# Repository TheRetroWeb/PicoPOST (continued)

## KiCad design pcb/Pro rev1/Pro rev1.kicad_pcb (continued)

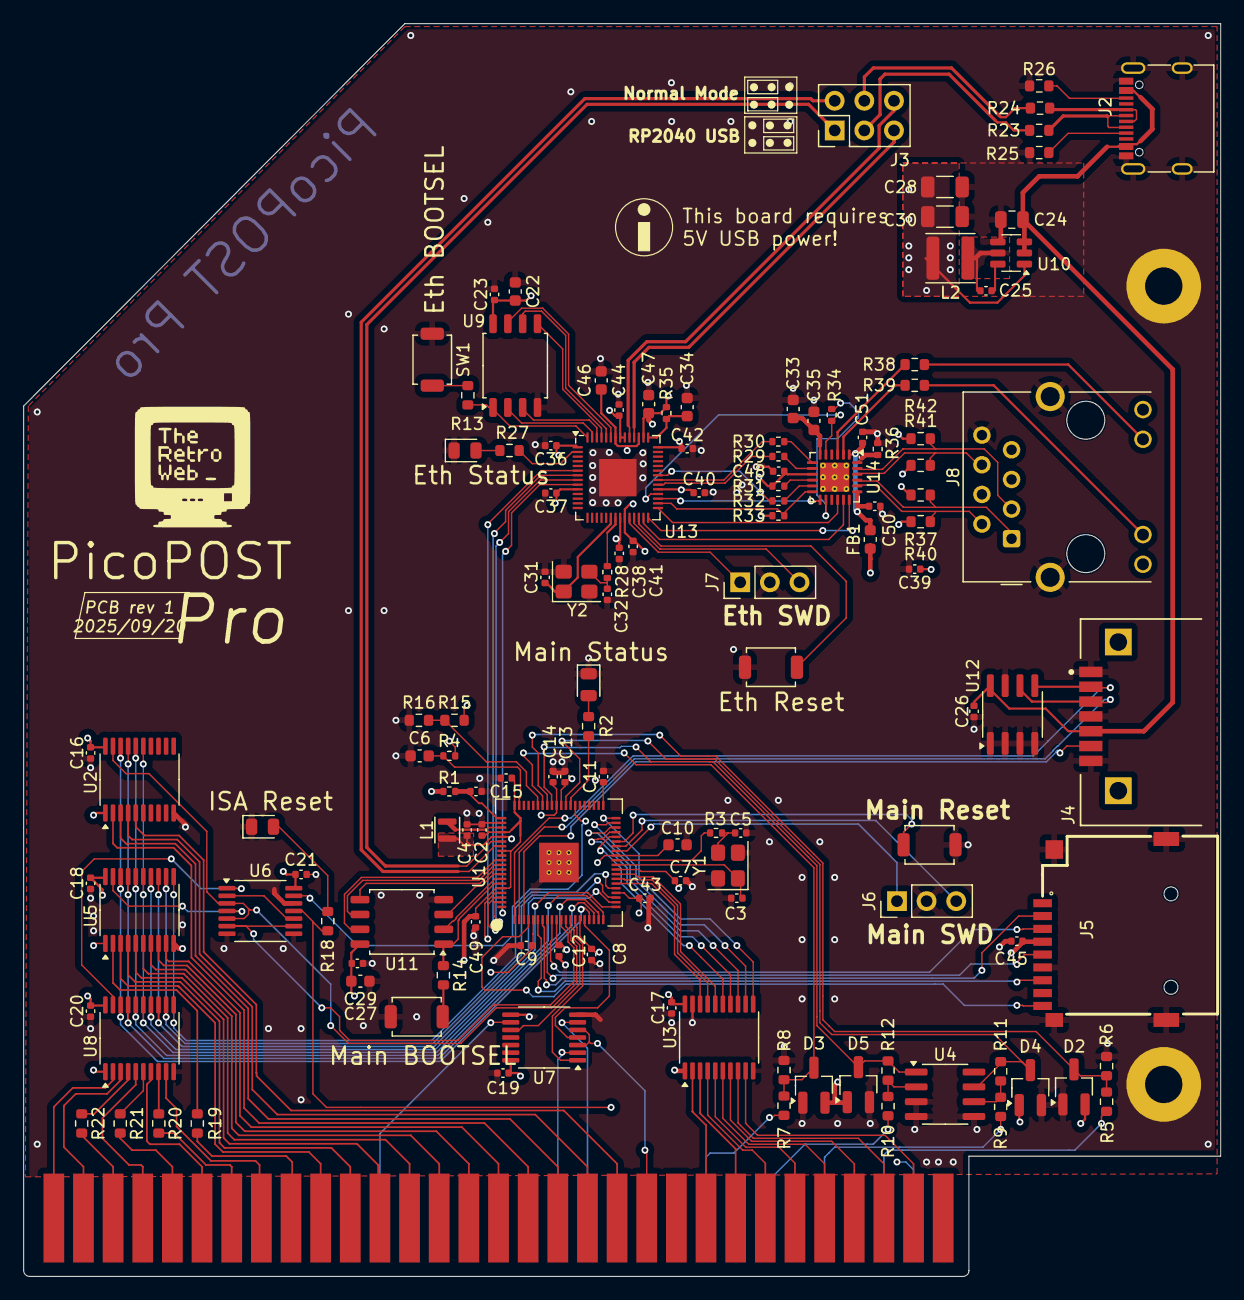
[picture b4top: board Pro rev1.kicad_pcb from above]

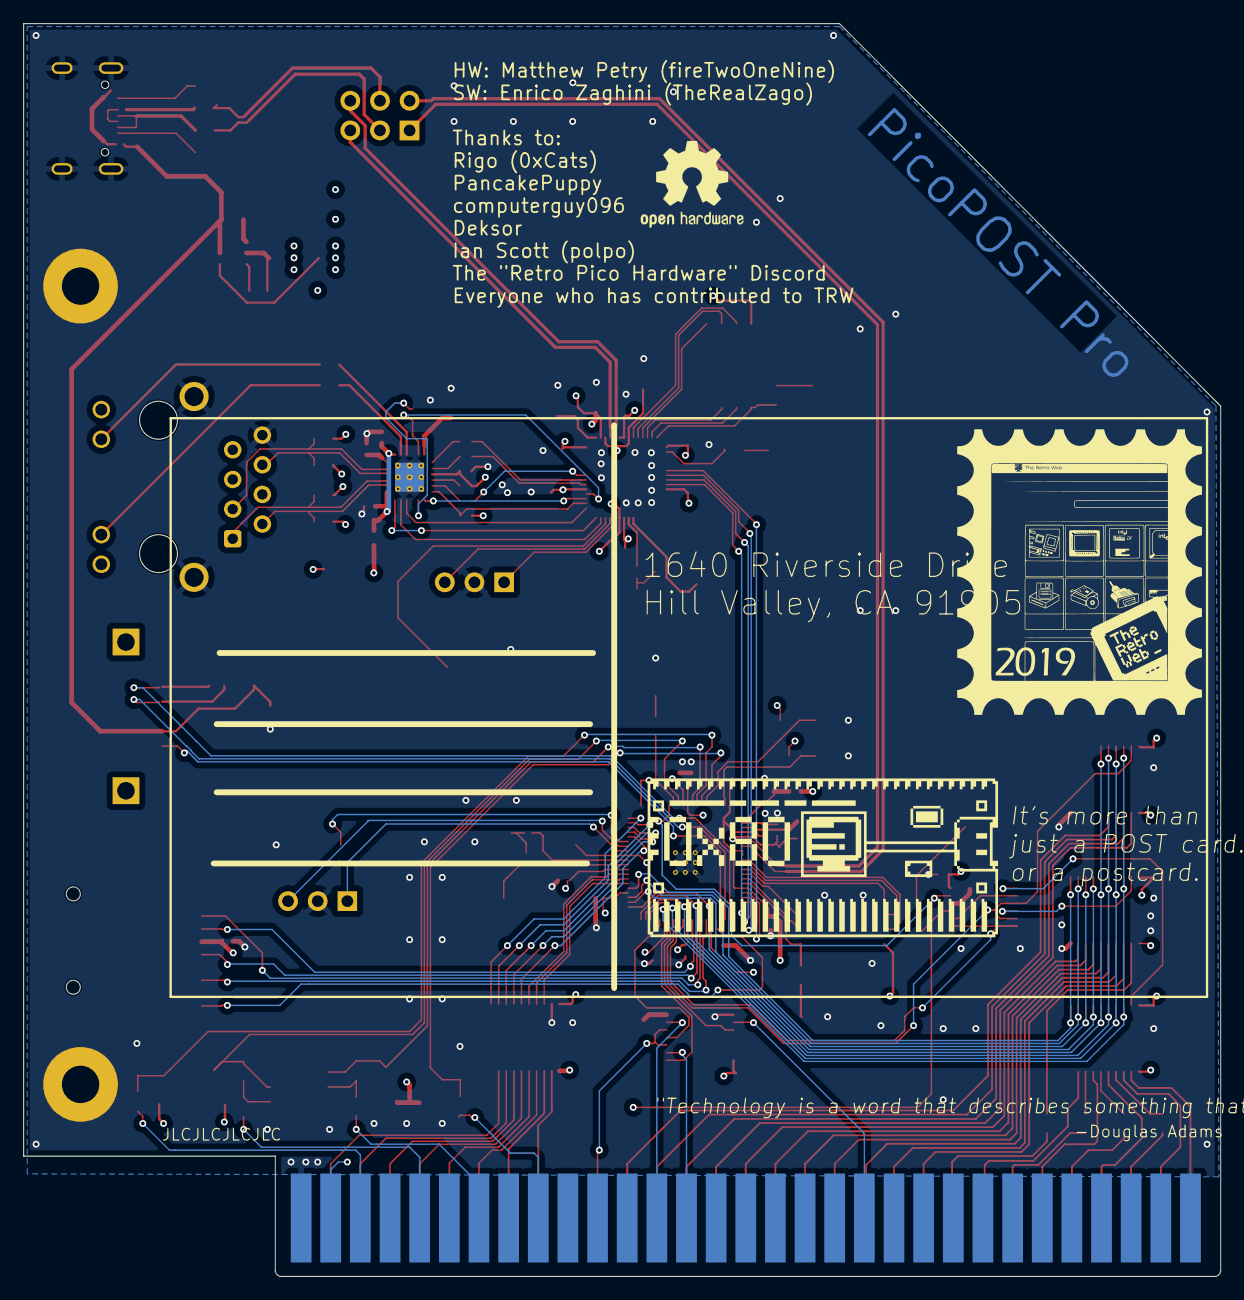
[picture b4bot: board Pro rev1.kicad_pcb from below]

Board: 4 copper layers, 102.6 x 107.3 mm, 135 parts (2 on the bottom side), 162 nets.

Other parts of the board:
.: LOGO; TRW_logo
.#2: LOGO; postcard_stamp
.#3: LOGO; picopost_logo

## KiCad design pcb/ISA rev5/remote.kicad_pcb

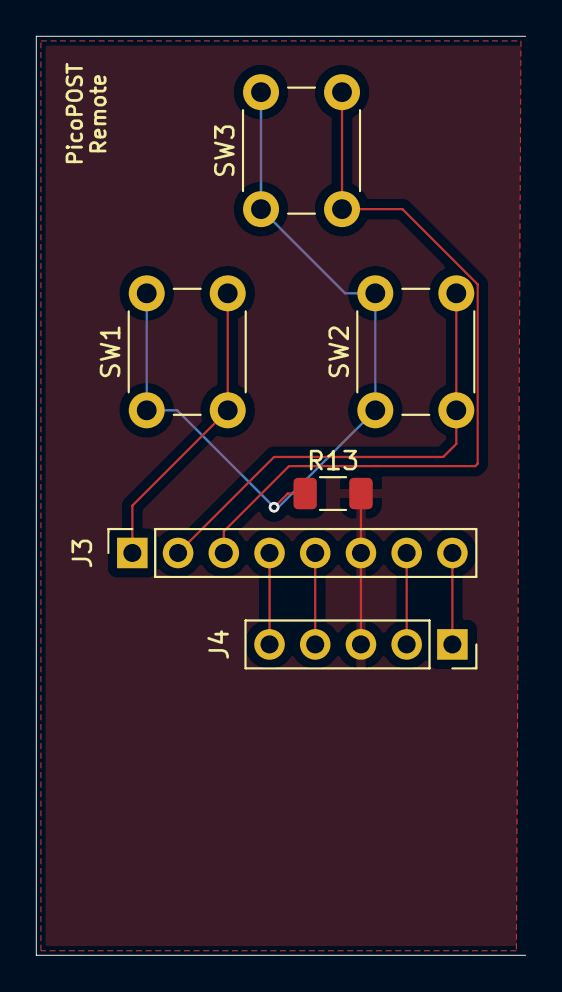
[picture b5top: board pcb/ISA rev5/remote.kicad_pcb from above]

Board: 2 copper layers, 27.2 x 51.1 mm, 6 parts (0 on the bottom side), 9 nets.

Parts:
J3: remote header; PinSocket_1x08_P2.54mm_Vertical
J4: OLED here; PinSocket_1x05_P2.54mm_Vertical
R13: 1000; R_1206_3216Metric_Pad1.30x1.75mm_HandSolder
SW1: Up; SW_PUSH_6mm_H5mm
SW2: Down; SW_PUSH_6mm_H5mm
SW3: Select/Menu; SW_PUSH_6mm_H5mm

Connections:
/remote_GND: J3.6, J4.3, R13.2
unnamed: J3.1, SW1.2
unnamed: J3.2, SW2.2
unnamed: J3.3, SW3.2
unnamed: J3.4, J4.5
unnamed: J3.5, J4.4
unnamed: J3.7, J4.2
unnamed: J3.8, J4.1
unnamed: R13.1, SW1.1, SW2.1, SW3.1

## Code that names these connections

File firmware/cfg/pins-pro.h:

/**
 * @file pins-pro.h
 * @brief Pin definitions for the Pro RP2350-based board
 */

#ifndef PICOPOST_DEF_PINS_PRO
#define PICOPOST_DEF_PINS_PRO

#define PIN_ISA_D0 25
#define PIN_ISA_D1 26
#define PIN_ISA_D2 27
#define PIN_ISA_D3 28
#define PIN_ISA_D4 29
#define PIN_ISA_D5 30
#define PIN_ISA_D6 31
#define PIN_ISA_D7 32

#define PIN_ISA_A0 17
#define PIN_ISA_A1 18
#define PIN_ISA_A2 19
#define PIN_ISA_A3 20
#define PIN_ISA_A4 21
#define PIN_ISA_A5 22
#define PIN_ISA_A6 23
#define PIN_ISA_A7 24
#define PIN_ISA_A8 17
#define PIN_ISA_A9 18
#define PIN_ISA_A10 19
#define PIN_ISA_A11 20
#define PIN_ISA_A12 21
#define PIN_ISA_A13 22
#define PIN_ISA_A14 23
#define PIN_ISA_A15 24
#define PIN_ISA_A16 17
#define PIN_ISA_A17 18
#define PIN_ISA_A18 19
#define PIN_ISA_A19 20

#define PIN_ADDRESS_BANK_0 12
#define PIN_ADDRESS_BANK_1 13

#define PIN_ISA_BRDY_RD 15
#define PIN_ISA_BRDY_WR 16
#define PIN_ISA_CLK 14
#define PIN_ISA_RST 38

#define PIN_REMOTE_IRQ 6

// +5V monitor
#define PIN_5V_MON 42
#define ADC_5V_MON 2

// +12V monitor
#define PIN_12V_MON 43
#define ADC_12V_MON 3

#define PIN_I2C_SDA 4
#define PIN_I2C_SCL 5

#endif // PICOPOST_DEF_PINS_PRO

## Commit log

2022-06-17 initial file commit
2022-06-17 rev 2 ISA board
2022-06-17 README info
2022-06-18 more available 74LVC02 footprint; generate gbrs
2022-06-20 rev4 board
2022-06-26 Initial commit - Set up CMake compiler rules - Something about OLED testing - Bundling datasheets for completeness
2022-10-23 Added some more datasheets
2022-10-23 Switched to a 128x32 display by default
2022-11-04 Implemented basic serial readout - Does it work?
2022-11-11 Fixed incorrect bus activity detection and readout
2022-11-12 PCB revision 5
2022-11-14 PCB rev 5.1
2022-12-03 GPIO was the wrong approach - Removed the GPIO-based ISA bus handler library. Way too slow! - Brand new PIO-based read logic. Wicked fast!
    Smarter application handling
    - Provisioning for logic plugin selection
    - Implemented multi-core, queued serial print for Port 80h readout
2022-12-04 Registering reset events - Implemented reset status polling with the 2nd PIO instance - Recording timestamp since last reset, with microseconds precision. Prints in milliseconds.
2022-12-04 Implemented voltage monitoring - Reads 5V and 12V and prints to serial every 100ms - Precision is not really there. Use CALIB variables in CMake config for crude static adjustment.
2022-12-04 Revert to port 80 listener as default application
2022-12-05 OLED is displaying things! - Trashed old DIY OLED library - Added submodule for SSD1306 library - May add compatibility for SH1106 in the future - This library is C++... Renamed main.c so compiler do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
2022-12-06 Better port 80h experience - Keep track of the last 4 events - Better displaying of reset event - Don't stall out after 3 consecutive resets - Remove spurious reset PIO IRQ
2022-12-08 OLED & buttons UI - Split logic and UI operations into dedicated files - Implemented menu for selecting wanted working mode - Up+Down returns to menu - TODO: lost bus reset event!?!? - Converted ever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
2023-01-01 PCB rev6
2023-01-01 PCB rev 6 part deux
2023-01-02 [firmware] New OLED library - Forked previous library for SH1106 implementation
2023-01-02 final tweaks to rev6?
2023-01-02 [firmware] PCB v6 compatibility + QoL improvements - Added MCP23009 library - Naive PCB rev detection. If MCP23009 not found, assume it's v5. - If OLED not detected, wait for USB CDC to come up, then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
2023-01-02 final rev6 release
2023-01-02 Fattened readme
2023-01-02 [firmware] Fixed slightly broken key combos
2023-01-03 more README tweaks
2023-01-03 Create LICENSE file
2023-01-03 Updated README to match new licenses
2023-01-05 [firmware] Added VSCode debug support - See official documentation for setup
2023-01-05 [firmware] Updated OLED library
2023-01-05 [firmware] New features and improvements - Implemented 84h, 90h, 300h and 378h readers - Using contextual menu a bit better - Provisioning for -12V rail monitoring - Custom pages for 128x32 and 128x6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
2023-01-15 [firmware] Testing on rev 6 hw - Redone main entrypoint and basic multicore logic as C++ class - Improved UI and keypad handling - Updated MCP pin and registers definitions - Simplified MCP discovery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
2023-02-13 Updated readme
    - Added reference to blog post
2023-03-01 Updated PDF schematic for rev6 - Now has both interface board and remote (still wrong wiring tho)
2023-03-01 [pcb] Fixed pinout mistake on remote connector
2023-03-01 Rev7 (final?) PCB
2023-03-02 rev7 schematic pdfs
2023-03-31 Finalized rev7 including gerbers
2023-04-25 [firmware] Now with 50% less suckiness - Fixing code style after a pass in SonarLint - Using scoped enumerations where it makes sense - Marked noreturn functions as such - (Temporarily?) Removed supp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
2023-04-29 [firmware] It lives! - Removed hard-wired SDK path from CMake rules. Use environment variables instead - Added handy jump-to-bootloader menu item - Swapped tasks to other core, so UI is on core0 and 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
2023-05-01 [firmware] Extra bling! - Bumped patch number, version 0.4.1 - Added PicoPOST bitmap drawing from official documentation as landing Info banner - Retouched icon drawing logic so it's a bit more flexi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
2023-05-02 [firmware] Bells & whistles - OLED now smoothly dims after 15 seconds of inactivity - Timing set at compile time with CMake define - Fixed crash on reader exit due to double PIO abort trigger - Reset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
2023-05-05 [firmware] Make 'em toasters fly! - Added simple 3-frame Flying Toasters! sprite and motion pattern - Screen ALWAYS dims after 15s of inactivity (from user and from inputs) - When in menu, switch to 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
2023-05-14 GitHub is dumb with video embeds
2023-05-14 GitHub is very dumb with video embeds
2023-05-14 GitHub is extremely dumb with video embeds
2023-06-02 [firmware] Added compile option for PC/104 PCB prototype - Removed references for old rev5 PCB
2023-06-09 [firmware] Fallback output to USB serial - Defaults to port 80h reader
2023-06-09 [firmware] CMake building environment - Added option to set No-Remote operation, it toggles between port 80h reader fallback and halting - Making the resulting UF2 file named a bit smarter
2023-08-27 [firmware] Brain got tired with -12V input - Spice simulations suggest a mostly linear correlation in the active ADC range for our -12V solution - Using more precise and clearer coefficients in volta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
2023-08-28 [firmware] Fixed messed up CMake option checking
2023-12-27 [firmware] First ugly attempt at getting reset pulse to work again
2023-12-27 [firmware] Reset detect works and bus read has been restored! - Bumped firmware to revision 0.5.0 - TODO: HW needs a minor fix to include IOCHRDY to the read trigger logic - Added queue data flag for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
2023-12-28 [firmware] Added a few NOPs to let bus transcievers settle down during address bank switching
2023-12-28 [firmware] Optimized OLED buffer write routine - Instead of writing one queue point at a time, empty queue immediately and send all to draw routine - Only run expensive OLED buffer operations when al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
2023-12-28 [firmware] Optional compile flag for OC'ing RP2040 to 200 MHz
2023-12-28 [firmware] Figuring out address byte mangling and missing data - In fast transaction bursts, we are missing some data because the PIO stalls, after filling the 8 FIFO buffers with no one emptying the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
2024-01-16 ISA rev8 preliminary
2024-01-21 [firmware] Partially matching PCB rev 8 - Removed -12V reader. It will never work right :woeisme: - Undoing VCF edits
2024-01-21 rev8 PCB final?
2025-03-22 [firmware] Dropped -12V readout, it just doesn't work
2025-03-22 [firmware] Start right into port 80h reader, as it's the most common scenario
2025-03-22 [firmware] WIP - DOES NOT WORK - Try to use DMA to avoid stalling PIO if logic can't dispatch codes fast enough
2025-08-05 [firmware] Cherry-picked some QoL improvements from c19cab9b25e95cfa58e91134193ed29827b2cf8e and 4f9cfd7caee2a9bf3e65bb627b598a174af2321b
2025-08-06 [firmware] Updated layout to make use of official Raspberry Pi Pico VSCode extension
2025-08-06 [firmware] It didn't need DMA, after all - Dropped all references to DMA setup - Also dropped all references to mutex experiment - Temporarily disabled reset pulse reader - Use PIO FIFO IRQ to quickl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
2025-08-07 [firmware] Added back reset pulse detection via ISR - Split bus reader ISRs between address-filtered and unfiltered acquisition
2025-08-07 Update README.md, again
2025-08-07 [firmware] Fixed weird memory leak with old-school array, replaced by std::vector
2025-08-07 [firmware] Fixed hang when exiting and re-entering bus readers
2025-08-07 [firmware] Fixed mode change never working due to exit request flag always stuck active at all times
2025-08-10 [firmware] Actually fixed unstable operation due to misconfigured overclocking - Just definitions are not enough, we need to inject our own board definition to correctly configure SPI flash clock div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
2025-08-16 preliminary Pro design files
2025-08-24 updates and fixes to Pro rev1 PCB, possibly prod-ready?
2025-10-02 Pro rev1 complete
2025-10-07 [firmware] First draft for Pro rev1 support
